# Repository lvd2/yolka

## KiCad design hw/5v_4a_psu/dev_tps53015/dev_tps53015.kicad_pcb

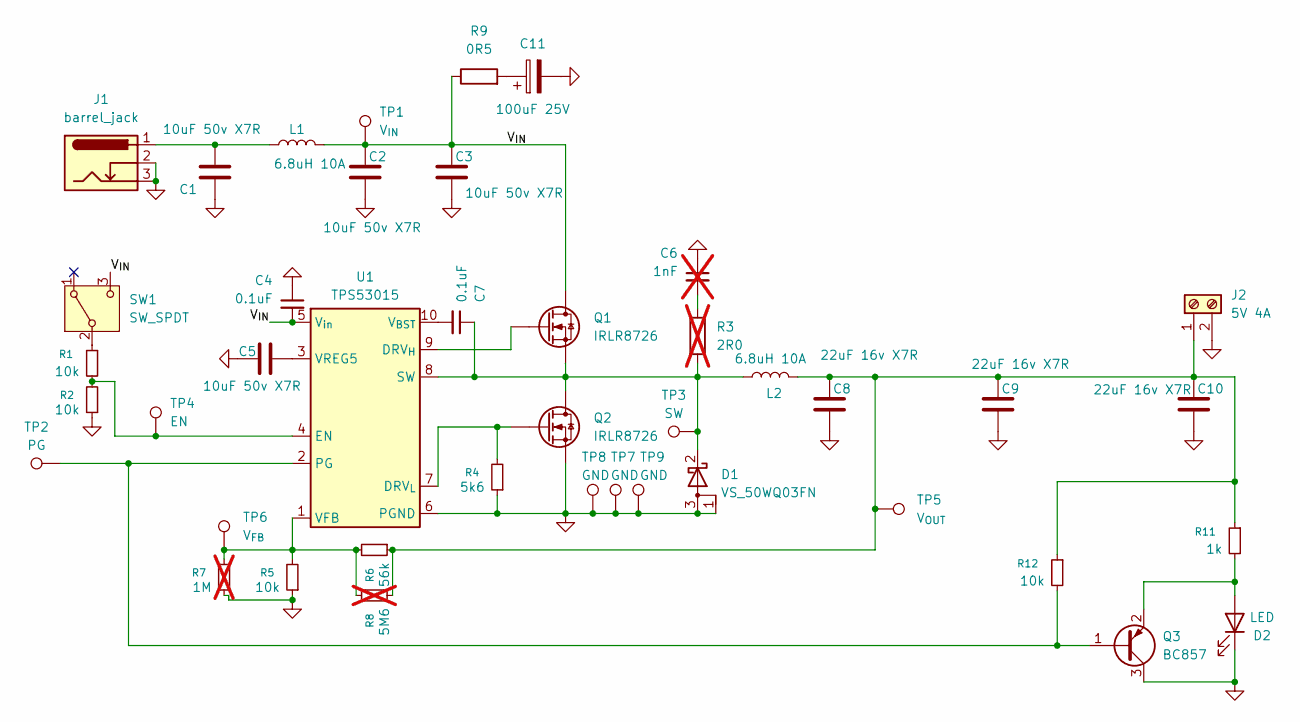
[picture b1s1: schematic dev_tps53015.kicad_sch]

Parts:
C1, C2, C3, C5: 10uF 50v X7R; C_1210_3225Metric_Pad1.33x2.70mm_HandSolder
C4, C7: 0.1uF; C_0805_2012Metric_Pad1.18x1.45mm_HandSolder
C6: 1nF; C_0805_2012Metric_Pad1.18x1.45mm_HandSolder; not fitted
C8, C9, C10: 22uF 16v X7R; C_1210_3225Metric_Pad1.33x2.70mm_HandSolder
C11: 100uF 25V; CP_Radial_D6.3mm_P2.50mm
D1: VS_50WQ03FN; TO-252-2
D2: LED; LED_0805_2012Metric
J1: barrel_jack; BarrelJack_Horizontal
J2: 5V 4A; KF7.62-2
L1, L2: 6.8uH 10A; univ_12x12_inductor
Q1, Q2: IRLR8726; TO-252-FET
Q3: BC857; SOT-23_Handsoldering
R1, R2, R5, R12: 10k; R_0805_2012Metric_Pad1.20x1.40mm_HandSolder
R3: 2R0; R_1206_3216Metric_Pad1.30x1.75mm_HandSolder; not fitted
R4: 5k6; R_0805_2012Metric_Pad1.20x1.40mm_HandSolder
R6: 56k; R_0805_2012Metric_Pad1.20x1.40mm_HandSolder
R7: 1M; R_0805_2012Metric_Pad1.20x1.40mm_HandSolder; not fitted
R8: 5M6; R_0805_2012Metric_Pad1.20x1.40mm_HandSolder; not fitted
R9: 0R5; R_1206_3216Metric_Pad1.30x1.75mm_HandSolder
R11: 1k; R_0805_2012Metric_Pad1.20x1.40mm_HandSolder
SW1: SW_SPDT; SW_SPDT_PCM12
TP1: V_{IN}; PinHeader_1x01_P2.54mm_Vertical
TP2: PG; PinHeader_1x01_P2.54mm_Vertical
TP3: SW; PinHeader_1x01_P2.54mm_Vertical
TP4: EN; PinHeader_1x01_P2.54mm_Vertical
TP5: V_{OUT}; PinHeader_1x01_P2.54mm_Vertical
TP6: V_{FB}; PinHeader_1x01_P2.54mm_Vertical
TP7, TP8, TP9: GND; PinHeader_1x01_P2.54mm_Vertical
U1: TPS53015; VSSOP-10_3x3mm_P0.5mm

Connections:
/V_{IN}: C2.1, C3.1, C4.2, L1.2, Q1.D, R9.1, SW1.3 (C), TP1.1, U1.5 (V_{in})
GND: C1.2, C2.2, C3.2, C4.1, C5.2, C6.1, C8.2, C9.2, C10.2, C11.2, D1.1 (A), D1.3 (A), D2.1 (K), J1.2, J1.3, J2.2, Q2.S, Q3.3 (C), R2.1, R4.1, R5.1, R7.1, SW1.4, TP7.1, TP8.1, TP9.1, U1.6 (PGND)
unnamed: C1.1, J1.1, L1.1
unnamed: C6.2, R3.1
unnamed: C11.1, R9.2
unnamed: C7.1, D1.2 (K), L2.1, Q1.S, Q2.D, R3.2, TP3.1, U1.8 (SW)
unnamed: D2.2 (A), Q3.2 (E), R11.2
unnamed: C8.1, C9.1, C10.1, J2.1, L2.2, R6.1, R8.1, R11.1, R12.1, TP5.1
unnamed: Q3.1 (B), R12.2, TP2.1, U1.2 (PG)
unnamed: R1.1, SW1.2 (B)
unnamed: Q1.G, U1.9 (DRV_{H})
unnamed: Q2.G, R4.2, U1.7 (DRV_{L})
unnamed: R1.2, R2.2, TP4.1, U1.4 (EN)
unnamed: R5.2, R6.2, R7.2, R8.2, TP6.1, U1.1 (VFB)
unnamed: C5.1, U1.3 (VREG5)
unnamed: C7.2, U1.10 (V_{BST})

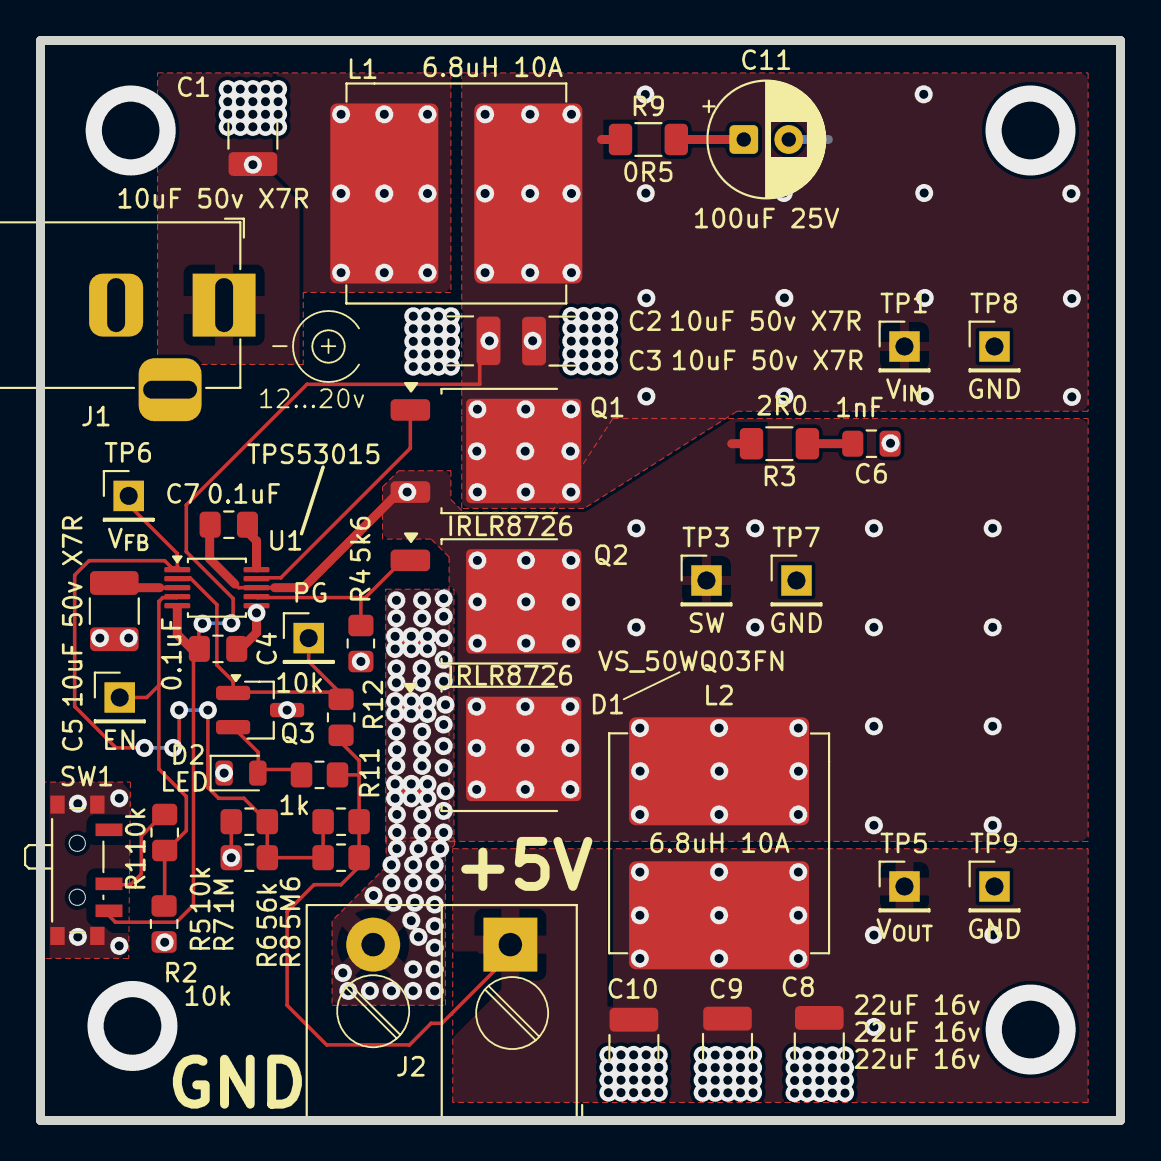
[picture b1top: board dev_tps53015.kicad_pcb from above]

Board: 2 copper layers, 60.0 x 60.0 mm, 42 parts (0 on the bottom side), 16 nets.

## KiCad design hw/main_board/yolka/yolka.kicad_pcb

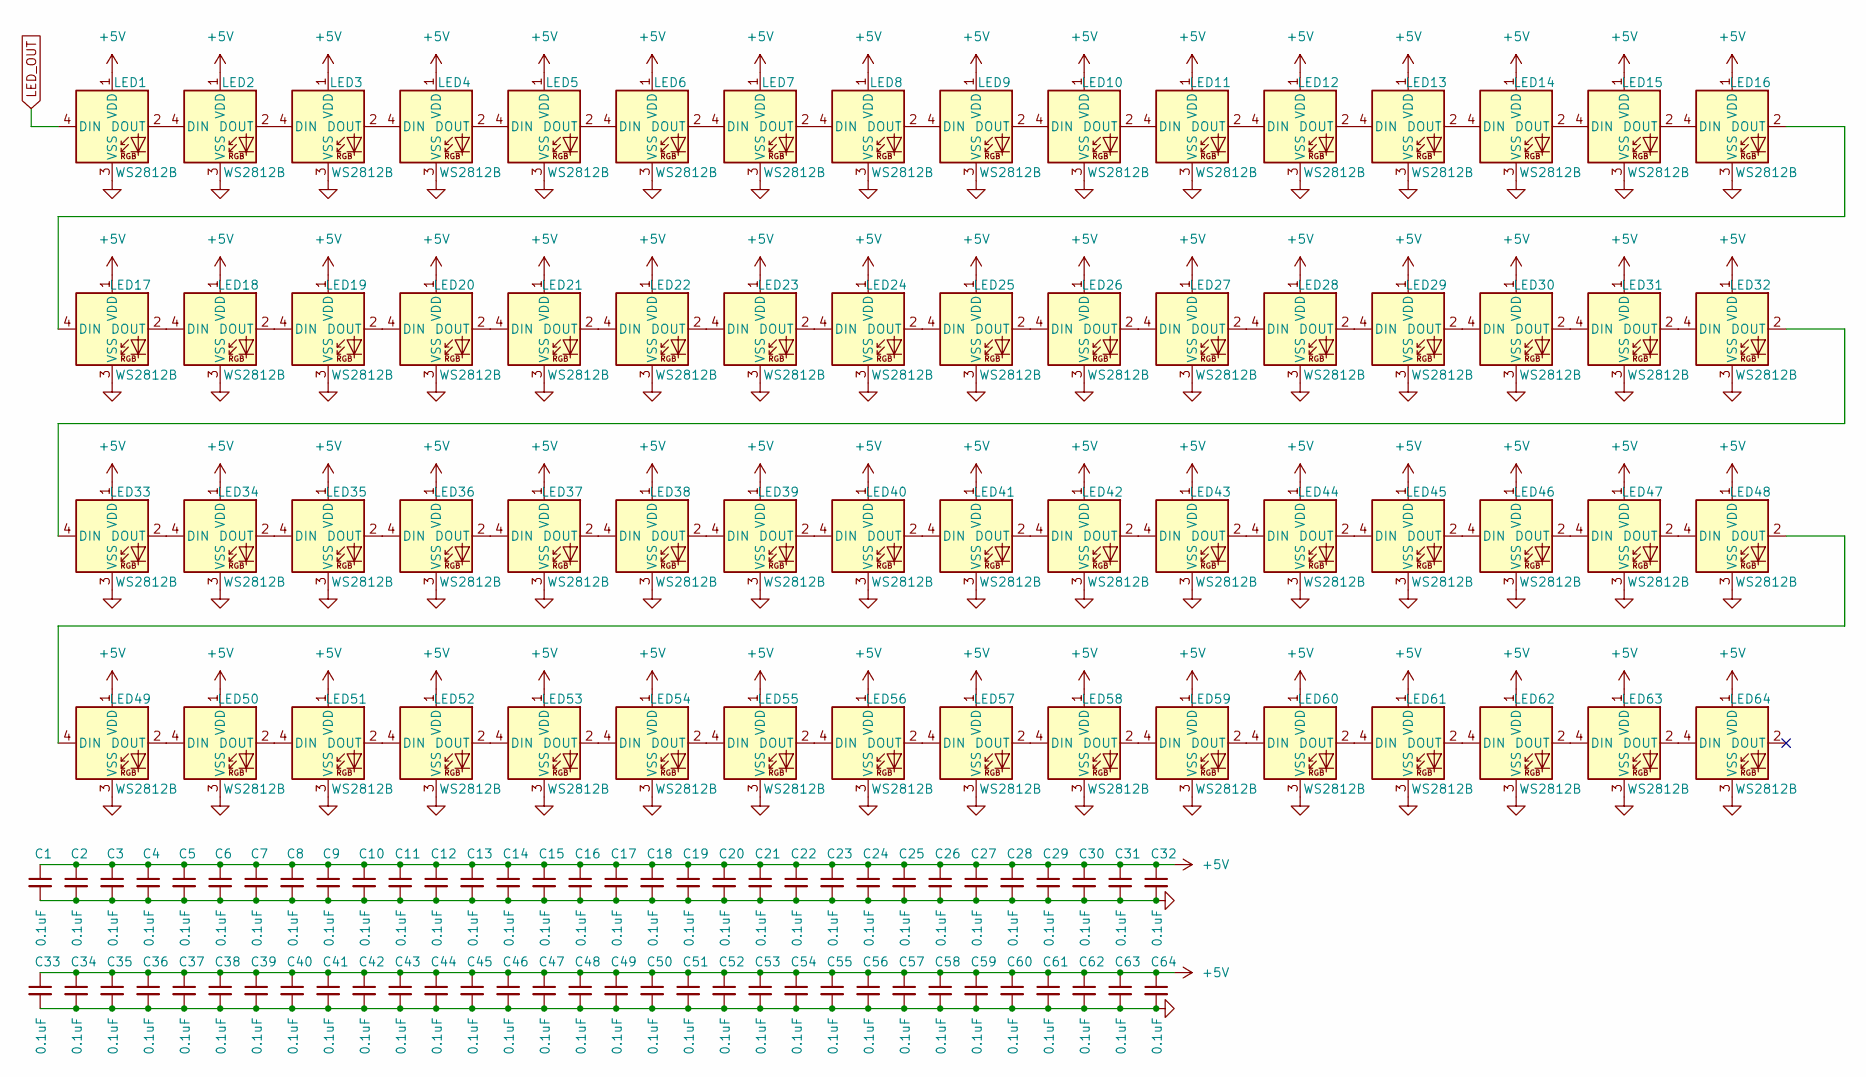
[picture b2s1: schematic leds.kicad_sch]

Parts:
C1, C2, C3, C4, C5, C6, C7, C8, C9, C10, C11, C12, C13, C14, C15, C16, C17, C18, C19, C20, C21, C22, C23, C24, C25, C26, C27, C28, C29, C30, C31, C32, C33, C34, C35, C36, C37, C38, C39, C40, C41, C42, C43, C44, C45, C46, C47, C48, C49, C50, C51, C52, C53, C54, C55, C56, C57, C58, C59, C60, C61, C62, C63, C64: 0.1uF; C_0805_2012Metric_Pad1.18x1.45mm_HandSolder
LED1, LED2, LED3, LED4, LED5, LED6, LED7, LED8, LED9, LED10, LED11, LED12, LED13, LED14, LED15, LED16, LED17, LED18, LED19, LED20, LED21, LED22, LED23, LED24, LED25, LED26, LED27, LED28, LED29, LED30, LED31, LED32, LED33, LED34, LED35, LED36, LED37, LED38, LED39, LED40, LED41, LED42, LED43, LED44, LED45, LED46, LED47, LED48, LED49, LED50, LED51, LED52, LED53, LED54, LED55, LED56, LED57, LED58, LED59, LED60, LED61, LED62, LED63, LED64: WS2812B; LED_WS2812B_PLCC4_5.0x5.0mm_P3.2mm

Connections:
+5V: C1.1, C2.1, C3.1, C4.1, C5.1, C6.1, C7.1, C8.1, C9.1, C10.1, C11.1, C12.1, C13.1, C14.1, C15.1, C16.1, C17.1, C18.1, C19.1, C20.1, C21.1, C22.1, C23.1, C24.1, C25.1, C26.1, C27.1, C28.1, C29.1, C30.1, C31.1, C32.1, C33.1, C34.1, C35.1, C36.1, C37.1, C38.1, C39.1, C40.1, C41.1, C42.1, C43.1, C44.1, C45.1, C46.1, C47.1, C48.1, C49.1, C50.1, C51.1, C52.1, C53.1, C54.1, C55.1, C56.1, C57.1, C58.1, C59.1, C60.1, C61.1, C62.1, C63.1, C64.1, LED1.1 (VDD), LED2.1 (VDD), LED3.1 (VDD), LED4.1 (VDD), LED5.1 (VDD), LED6.1 (VDD), LED7.1 (VDD), LED8.1 (VDD), LED9.1 (VDD), LED10.1 (VDD), LED11.1 (VDD), LED12.1 (VDD), LED13.1 (VDD), LED14.1 (VDD), LED15.1 (VDD), LED16.1 (VDD), LED17.1 (VDD), LED18.1 (VDD), LED19.1 (VDD), LED20.1 (VDD), LED21.1 (VDD), LED22.1 (VDD), LED23.1 (VDD), LED24.1 (VDD), LED25.1 (VDD), LED26.1 (VDD), LED27.1 (VDD), LED28.1 (VDD), LED29.1 (VDD), LED30.1 (VDD), LED31.1 (VDD), LED32.1 (VDD), LED33.1 (VDD), LED34.1 (VDD), LED35.1 (VDD), LED36.1 (VDD), LED37.1 (VDD), LED38.1 (VDD), LED39.1 (VDD), LED40.1 (VDD), LED41.1 (VDD), LED42.1 (VDD), LED43.1 (VDD), LED44.1 (VDD), LED45.1 (VDD), LED46.1 (VDD), LED47.1 (VDD), LED48.1 (VDD), LED49.1 (VDD), LED50.1 (VDD), LED51.1 (VDD), LED52.1 (VDD), LED53.1 (VDD), LED54.1 (VDD), LED55.1 (VDD), LED56.1 (VDD), LED57.1 (VDD), LED58.1 (VDD), LED59.1 (VDD), LED60.1 (VDD), LED61.1 (VDD), LED62.1 (VDD), LED63.1 (VDD), LED64.1 (VDD); also elsewhere on the board
GND: C1.2, C2.2, C3.2, C4.2, C5.2, C6.2, C7.2, C8.2, C9.2, C10.2, C11.2, C12.2, C13.2, C14.2, C15.2, C16.2, C17.2, C18.2, C19.2, C20.2, C21.2, C22.2, C23.2, C24.2, C25.2, C26.2, C27.2, C28.2, C29.2, C30.2, C31.2, C32.2, C33.2, C34.2, C35.2, C36.2, C37.2, C38.2, C39.2, C40.2, C41.2, C42.2, C43.2, C44.2, C45.2, C46.2, C47.2, C48.2, C49.2, C50.2, C51.2, C52.2, C53.2, C54.2, C55.2, C56.2, C57.2, C58.2, C59.2, C60.2, C61.2, C62.2, C63.2, C64.2, LED1.3 (VSS), LED2.3 (VSS), LED3.3 (VSS), LED4.3 (VSS), LED5.3 (VSS), LED6.3 (VSS), LED7.3 (VSS), LED8.3 (VSS), LED9.3 (VSS), LED10.3 (VSS), LED11.3 (VSS), LED12.3 (VSS), LED13.3 (VSS), LED14.3 (VSS), LED15.3 (VSS), LED16.3 (VSS), LED17.3 (VSS), LED18.3 (VSS), LED19.3 (VSS), LED20.3 (VSS), LED21.3 (VSS), LED22.3 (VSS), LED23.3 (VSS), LED24.3 (VSS), LED25.3 (VSS), LED26.3 (VSS), LED27.3 (VSS), LED28.3 (VSS), LED29.3 (VSS), LED30.3 (VSS), LED31.3 (VSS), LED32.3 (VSS), LED33.3 (VSS), LED34.3 (VSS), LED35.3 (VSS), LED36.3 (VSS), LED37.3 (VSS), LED38.3 (VSS), LED39.3 (VSS), LED40.3 (VSS), LED41.3 (VSS), LED42.3 (VSS), LED43.3 (VSS), LED44.3 (VSS), LED45.3 (VSS), LED46.3 (VSS), LED47.3 (VSS), LED48.3 (VSS), LED49.3 (VSS), LED50.3 (VSS), LED51.3 (VSS), LED52.3 (VSS), LED53.3 (VSS), LED54.3 (VSS), LED55.3 (VSS), LED56.3 (VSS), LED57.3 (VSS), LED58.3 (VSS), LED59.3 (VSS), LED60.3 (VSS), LED61.3 (VSS), LED62.3 (VSS), LED63.3 (VSS), LED64.3 (VSS); also elsewhere on the board
LED_OUT: LED1.4 (DIN); also elsewhere on the board
unnamed: LED1.2 (DOUT), LED2.4 (DIN)
unnamed: LED2.2 (DOUT), LED3.4 (DIN)
unnamed: LED3.2 (DOUT), LED4.4 (DIN)
unnamed: LED4.2 (DOUT), LED5.4 (DIN)
unnamed: LED5.2 (DOUT), LED6.4 (DIN)
unnamed: LED6.2 (DOUT), LED7.4 (DIN)
unnamed: LED7.2 (DOUT), LED8.4 (DIN)
unnamed: LED8.2 (DOUT), LED9.4 (DIN)
unnamed: LED9.2 (DOUT), LED10.4 (DIN)
unnamed: LED10.2 (DOUT), LED11.4 (DIN)
unnamed: LED11.2 (DOUT), LED12.4 (DIN)
unnamed: LED12.2 (DOUT), LED13.4 (DIN)
unnamed: LED13.2 (DOUT), LED14.4 (DIN)
unnamed: LED14.2 (DOUT), LED15.4 (DIN)
unnamed: LED15.2 (DOUT), LED16.4 (DIN)
unnamed: LED16.2 (DOUT), LED17.4 (DIN)
unnamed: LED17.2 (DOUT), LED18.4 (DIN)
unnamed: LED18.2 (DOUT), LED19.4 (DIN)
unnamed: LED19.2 (DOUT), LED20.4 (DIN)
unnamed: LED20.2 (DOUT), LED21.4 (DIN)
unnamed: LED21.2 (DOUT), LED22.4 (DIN)
unnamed: LED22.2 (DOUT), LED23.4 (DIN)
unnamed: LED23.2 (DOUT), LED24.4 (DIN)
unnamed: LED24.2 (DOUT), LED25.4 (DIN)
unnamed: LED25.2 (DOUT), LED26.4 (DIN)
unnamed: LED26.2 (DOUT), LED27.4 (DIN)
unnamed: LED27.2 (DOUT), LED28.4 (DIN)
unnamed: LED28.2 (DOUT), LED29.4 (DIN)
unnamed: LED29.2 (DOUT), LED30.4 (DIN)
unnamed: LED30.2 (DOUT), LED31.4 (DIN)
unnamed: LED31.2 (DOUT), LED32.4 (DIN)
unnamed: LED32.2 (DOUT), LED33.4 (DIN)
unnamed: LED33.2 (DOUT), LED34.4 (DIN)
unnamed: LED34.2 (DOUT), LED35.4 (DIN)
unnamed: LED35.2 (DOUT), LED36.4 (DIN)
unnamed: LED36.2 (DOUT), LED37.4 (DIN)
unnamed: LED37.2 (DOUT), LED38.4 (DIN)
unnamed: LED38.2 (DOUT), LED39.4 (DIN)
unnamed: LED39.2 (DOUT), LED40.4 (DIN)
unnamed: LED40.2 (DOUT), LED41.4 (DIN)
unnamed: LED41.2 (DOUT), LED42.4 (DIN)
unnamed: LED42.2 (DOUT), LED43.4 (DIN)
unnamed: LED43.2 (DOUT), LED44.4 (DIN)
unnamed: LED44.2 (DOUT), LED45.4 (DIN)
unnamed: LED45.2 (DOUT), LED46.4 (DIN)
unnamed: LED46.2 (DOUT), LED47.4 (DIN)
unnamed: LED47.2 (DOUT), LED48.4 (DIN)
unnamed: LED48.2 (DOUT), LED49.4 (DIN)
unnamed: LED49.2 (DOUT), LED50.4 (DIN)
unnamed: LED50.2 (DOUT), LED51.4 (DIN)
unnamed: LED51.2 (DOUT), LED52.4 (DIN)
unnamed: LED52.2 (DOUT), LED53.4 (DIN)
unnamed: LED53.2 (DOUT), LED54.4 (DIN)
unnamed: LED54.2 (DOUT), LED55.4 (DIN)
unnamed: LED55.2 (DOUT), LED56.4 (DIN)
unnamed: LED56.2 (DOUT), LED57.4 (DIN)
unnamed: LED57.2 (DOUT), LED58.4 (DIN)
unnamed: LED58.2 (DOUT), LED59.4 (DIN)
unnamed: LED59.2 (DOUT), LED60.4 (DIN)
unnamed: LED60.2 (DOUT), LED61.4 (DIN)
unnamed: LED61.2 (DOUT), LED62.4 (DIN)
unnamed: LED62.2 (DOUT), LED63.4 (DIN)
unnamed: LED63.2 (DOUT), LED64.4 (DIN)

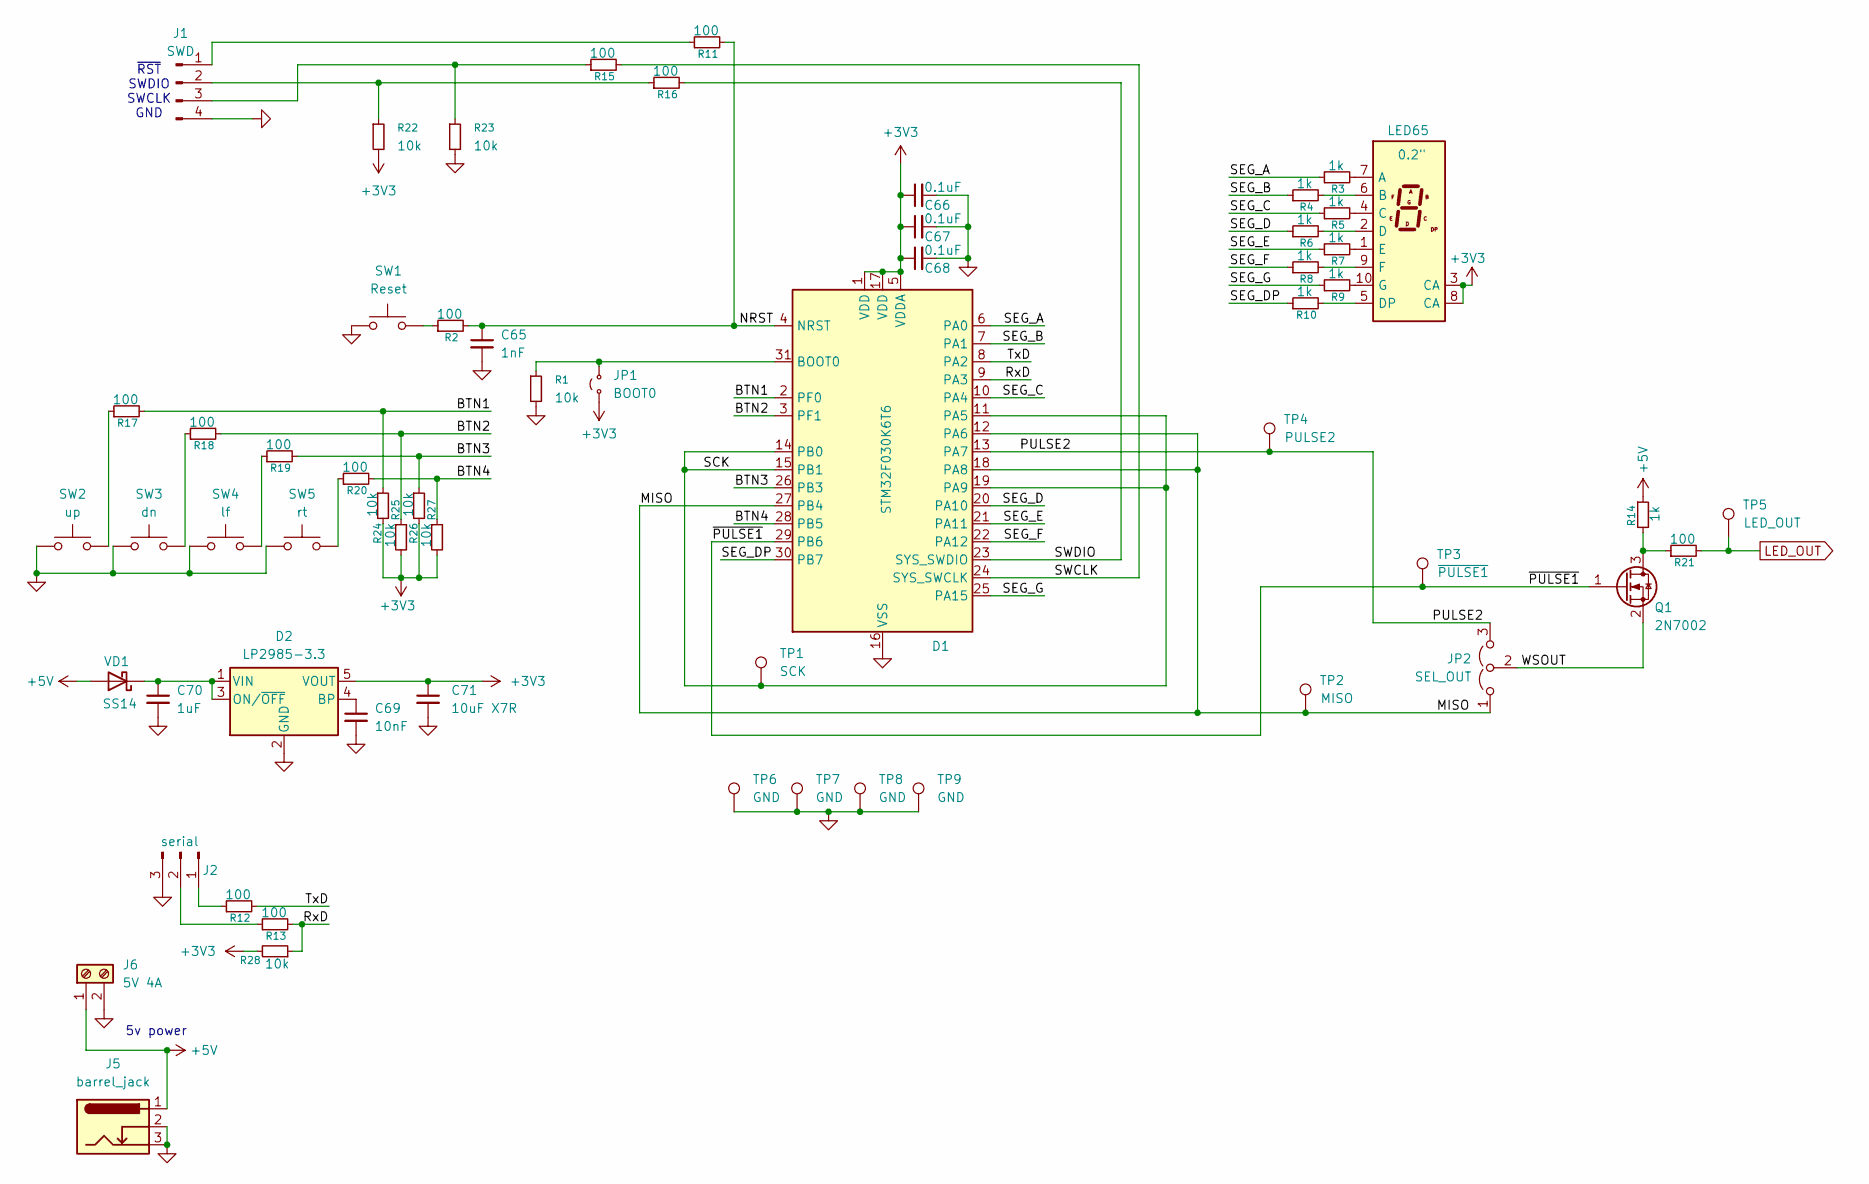
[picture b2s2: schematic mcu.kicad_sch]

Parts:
C65: 1nF; C_0805_2012Metric_Pad1.18x1.45mm_HandSolder
C66, C67, C68: 0.1uF; C_0805_2012Metric_Pad1.18x1.45mm_HandSolder
C69: 10nF; C_0805_2012Metric_Pad1.18x1.45mm_HandSolder
C70: 1uF; C_0805_2012Metric_Pad1.18x1.45mm_HandSolder
C71: 10uF X7R; C_1206_3216Metric_Pad1.33x1.80mm_HandSolder
D1: STM32F030K6T6; LQFP-32_7x7mm_P0.8mm
D2: LP2985-3.3; SOT-23-5
J1: SWD; PinHeader_1x04_P2.54mm_Horizontal
J2: serial; PinHeader_1x03_P2.54mm_Horizontal
J5: barrel_jack; BarrelJack_Horizontal
J6: 5V 4A; KF7.62-2
JP1: BOOT0; PinHeader_1x02_P2.54mm_Horizontal
JP2: SEL_OUT; PinHeader_1x03_P2.54mm_Horizontal
LED65: 0.2"; KCSC02-105
Q1: 2N7002; SOT-23
R1, R22, R23, R24, R25, R26, R27, R28: 10k; R_0805_2012Metric_Pad1.20x1.40mm_HandSolder
R2, R11, R12, R13, R15, R16, R17, R18, R19, R20, R21: 100; R_0805_2012Metric_Pad1.20x1.40mm_HandSolder
R3, R4, R5, R6, R7, R8, R9, R10, R14: 1k; R_0805_2012Metric_Pad1.20x1.40mm_HandSolder
SW1: Reset; SW_Push_1P1T_sunrom_7615
SW2: up; SW_Push_1P1T_sunrom_7615
SW3: dn; SW_Push_1P1T_sunrom_7615
SW4: lf; SW_Push_1P1T_sunrom_7615
SW5: rt; SW_Push_1P1T_sunrom_7615
TP1: SCK; PinHeader_1x01_P2.54mm_Vertical
TP2: MISO; PinHeader_1x01_P2.54mm_Vertical
TP3: ~{PULSE1}; PinHeader_1x01_P2.54mm_Vertical
TP4: PULSE2; PinHeader_1x01_P2.54mm_Vertical
TP5: LED_OUT; PinHeader_1x01_P2.54mm_Vertical
TP6, TP7, TP8, TP9: GND; PinHeader_1x01_P2.54mm_Vertical
VD1: SS14; D_SMA

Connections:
+3V3: C66.1, C67.1, C68.1, C71.1, D1.1 (VDD), D1.5 (VDDA), D1.17 (VDD), D2.5 (VOUT), JP1.1 (A), LED65.3 (CA), LED65.8 (CA), R22.2, R24.2, R25.2, R26.2, R27.2, R28.2
+5V: J5.1, J6.1, R14.1, VD1.2 (A); also elsewhere on the board
/MCU/BTN1: D1.2 (PF0), R17.2, R24.1
/MCU/BTN2: D1.3 (PF1), R18.2, R25.1
/MCU/BTN3: D1.26 (PB3), R19.2, R26.1
/MCU/BTN4: D1.28 (PB5), R20.2, R27.1
/MCU/MISO: D1.12 (PA6), D1.18 (PA8), D1.27 (PB4), JP2.1 (A), TP2.1
/MCU/NRST: C65.1, D1.4 (NRST), R2.2, R11.2
/MCU/PULSE2: D1.13 (PA7), JP2.3 (B), TP4.1
/MCU/RxD: D1.9 (PA3), R13.2, R28.1
/MCU/SCK: D1.11 (PA5), D1.14 (PB0), D1.15 (PB1), D1.19 (PA9), TP1.1
/MCU/SEG_A: D1.6 (PA0), R3.1
/MCU/SEG_B: D1.7 (PA1), R4.1
/MCU/SEG_C: D1.10 (PA4), R5.1
/MCU/SEG_D: D1.20 (PA10), R6.1
/MCU/SEG_DP: D1.30 (PB7), R10.1
/MCU/SEG_E: D1.21 (PA11), R7.1
/MCU/SEG_F: D1.22 (PA12), R8.1
/MCU/SEG_G: D1.25 (PA15), R9.1
/MCU/SWCLK: D1.24 (SYS_SWCLK), R15.2
/MCU/SWDIO: D1.23 (SYS_SWDIO), R16.2
/MCU/TxD: D1.8 (PA2), R12.2
/MCU/WSOUT: JP2.2 (C), Q1.2 (S)
/MCU/~PULSE1: D1.29 (PB6), Q1.1 (G), TP3.1
GND: C65.2, C66.2, C67.2, C68.2, C69.2, C70.2, C71.2, D1.16 (VSS), D1.32 (VSS), D2.2 (GND), J1.4, J2.3, J5.2, J5.3, J6.2, R1.2, R23.2, SW1.1, SW2.1, SW3.1, SW4.1, SW5.1, TP6.1, TP7.1, TP8.1, TP9.1; also elsewhere on the board
LED_OUT: R21.2, TP5.1; also elsewhere on the board
unnamed: D1.31 (BOOT0), JP1.2 (B), R1.1
unnamed: C69.1, D2.4 (BP)
unnamed: C70.1, D2.1 (VIN), D2.3 (ON/~OFF), VD1.1 (K)
unnamed: J1.1, R11.1
unnamed: J1.2, R16.1, R22.1
unnamed: J1.3, R15.1, R23.1
unnamed: J2.1, R12.1
unnamed: J2.2, R13.1
unnamed: LED65.7 (A), R3.2
unnamed: LED65.6 (B), R4.2
unnamed: LED65.4 (C), R5.2
unnamed: LED65.2 (D), R6.2
unnamed: LED65.5 (DP), R10.2
unnamed: LED65.1 (E), R7.2
unnamed: LED65.9 (F), R8.2
unnamed: LED65.10 (G), R9.2
unnamed: Q1.3 (D), R14.2, R21.1
unnamed: R2.1, SW1.2
unnamed: R17.1, SW2.2
unnamed: R18.1, SW3.2
unnamed: R19.1, SW4.2
unnamed: R20.1, SW5.2

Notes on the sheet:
5v power
~{RST} SWDIO SWCLK GND

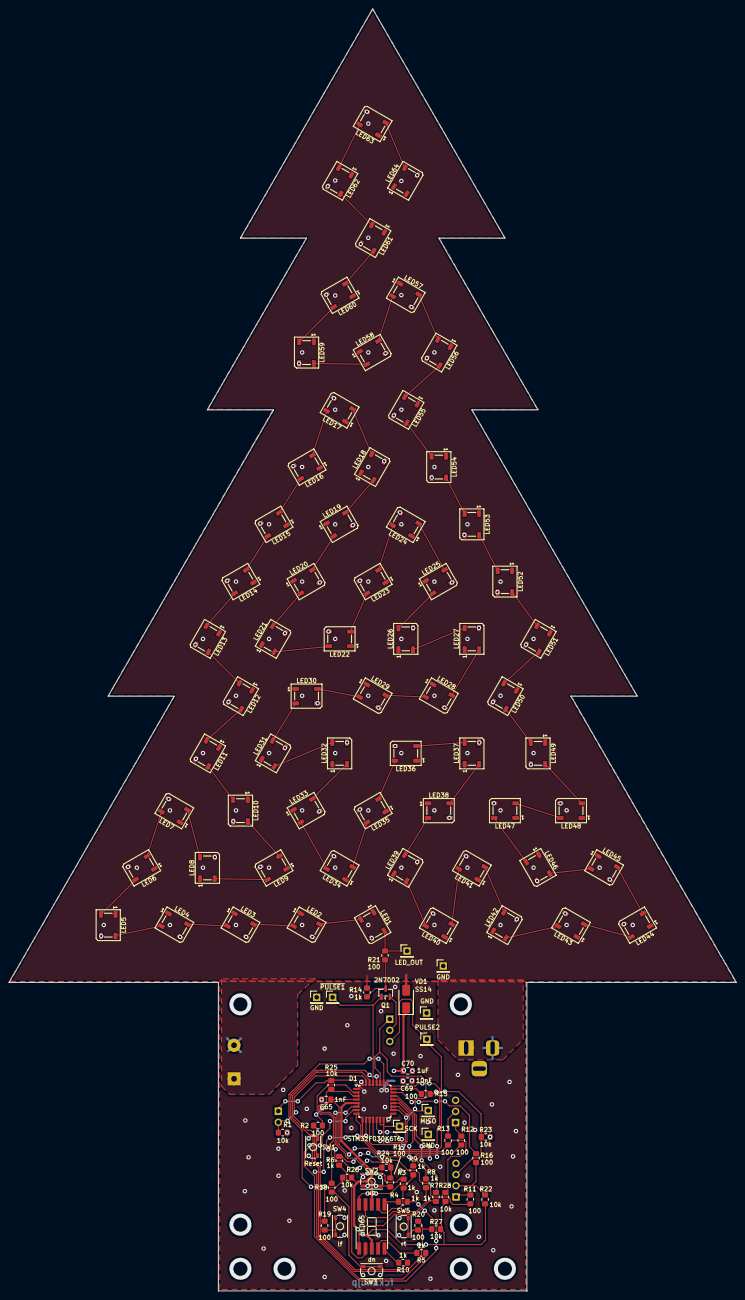
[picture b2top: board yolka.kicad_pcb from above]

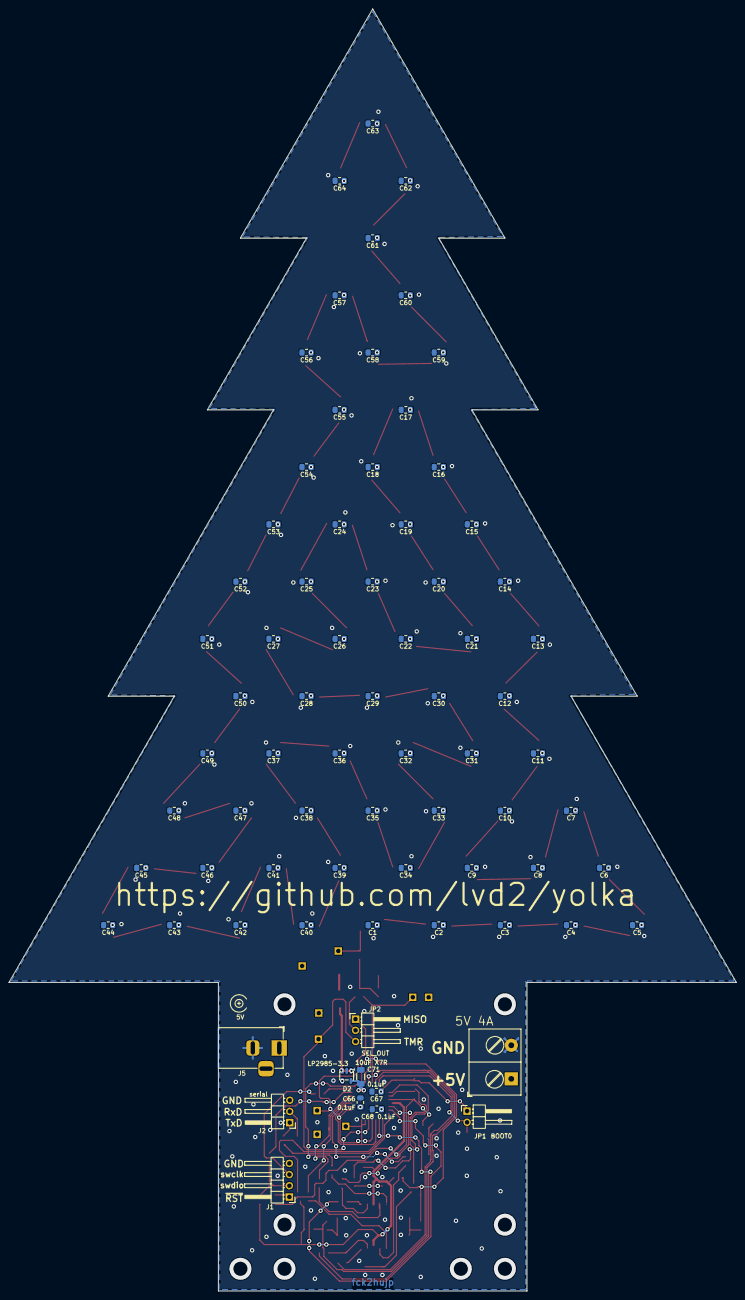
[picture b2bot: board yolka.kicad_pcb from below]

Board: 2 copper layers, 165.0 x 290.8 mm, 188 parts (75 on the bottom side), 111 nets.

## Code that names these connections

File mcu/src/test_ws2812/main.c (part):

#include <stdint.h>
#include "hw/stm32f0xx.h"

// PB6 -- set to 1 (fet gate)
// PB1 -- gen 3.2MHz clock (TIM14)
// PA5 -- input of 3.2 MHz for SPI1
// PA6 -- MISO from SPI1 (to ws2818)

//#define USE_XTAL 1
#define DO_DMA 1
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


	// PB6 as output emitting 1
	GPIOB->MODER &= ~GPIO_MODER_MODER6_Msk;
	GPIOB->MODER |= 1UL<<GPIO_MODER_MODER6_Pos; // general purpose output
	//
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	//
	GPIOB->BSRR = GPIO_BSRR_BS_6; // output 1

	// PA5 -- SPI1 SCK (input)
	// PA6 -- SPI1 MISO (output)
	GPIOA->MODER &= ~ (GPIO_MODER_MODER5 | GPIO_MODER_MODER6);
	GPIOA->MODER |= (2UL << GPIO_MODER_MODER5_Pos) |
	                (2UL << GPIO_MODER_MODER6_Pos) ;
	//
	GPIOA->OTYPER &= ~GPIO_OTYPER_OT_6; // push-pull (PA6)
	//
	GPIOA->OSPEEDR &= ~(GPIO_OSPEEDR_OSPEEDR5_Msk | GPIO_OSPEEDR_OSPEEDR6_Msk);   // 3rd speed grade
	GPIOA->OSPEEDR |= (2UL << GPIO_OSPEEDR_OSPEEDR6_Pos);                         //
	//
	GPIOA->AFR[0] = (GPIOA->AFR[0] & (~(GPIO_AFRL_AFRL5_Msk | GPIO_AFRL_AFRL6_Msk))) | (0UL << GPIO_AFRL_AFRL5_Pos) |  (0UL << GPIO_AFRL_AFRL6_Pos); // PA5,6 <- AF0



	// configure PB1 as output, controlled by TIM14
	GPIOB->MODER = (GPIOB->MODER & (~GPIO_MODER_MODER1_Msk)) | (2UL << GPIO_MODER_MODER1_Pos); // PB1 alternate function
	//
	GPIOB->OTYPER &= ~( GPIO_OTYPER_OT_1 );
	//
	GPIOB->OSPEEDR = (GPIOB->OSPEEDR & (~GPIO_OSPEEDR_OSPEEDR1_Msk)) | (2UL << GPIO_OSPEEDR_OSPEEDR1_Pos);
	//
	GPIOB->AFR[0] = (GPIOB->AFR[0] & (~GPIO_AFRL_AFRL1_Msk)) | (0UL << GPIO_AFRL_AFRL1_Pos); // PB1 <- AF0



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{
	phase++;

	if( GPIOA->IDR & GPIO_IDR_0 ) // check PA0
	{
		GPIOA->BSRR = GPIO_BSRR_BS_4; // set PA4
	}
	else
	{
		GPIOA->BSRR = GPIO_BSRR_BR_4; // clr PA4
	}


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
